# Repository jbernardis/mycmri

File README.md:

# mycmri
## DIY CMRI ecosystem for model railroad automation

This is very much a work in progress.  At this point, the following eagle designs are mature:

- blockocchexdelay - a single board with 6 DCC block occupancy detectors that immediately detect block entry, but do not report block exit until approximately 1 second after train actually leaves block.

- 2 byte input - a circuit design based on 74hc165 shift registers to pull in data from inputs such as buttons, block occupancy detectors, etc.

- 1 byte input - a 1 shift register version of the above.

- 2 byte output with darlington open collector with a darlington array in the output stream to support other devices such as motors and relays - circuit sink.

All other designs are very early in their life and have not been tested/debugged:

- node - an arduino based circuit that can shift in data from many inputs, shift out data to many outputs, drive servos through an adafruit PWM servo driver board, and report all of this back to a host PC (running JMRI?) via an RS485 bus.    This circuit may also provide 5 volt power to this ecosystem.

- 1 byte output version of the above

- relay boards designed to work with the output boards, 2 and 4 relay variants

- others as needs/inspirations arise.  Support for DCC Reverser and CD discharge unit is also being considered.

Arduino code will be provided as node functionality is implemented

Linux-based driver code is also part of this repository and is in very early development.

Slowly moving PCB design to kicad.  Both kicad and eagle designs will be included here, at least until the first boards are fabricated and tested from the kicad designs.

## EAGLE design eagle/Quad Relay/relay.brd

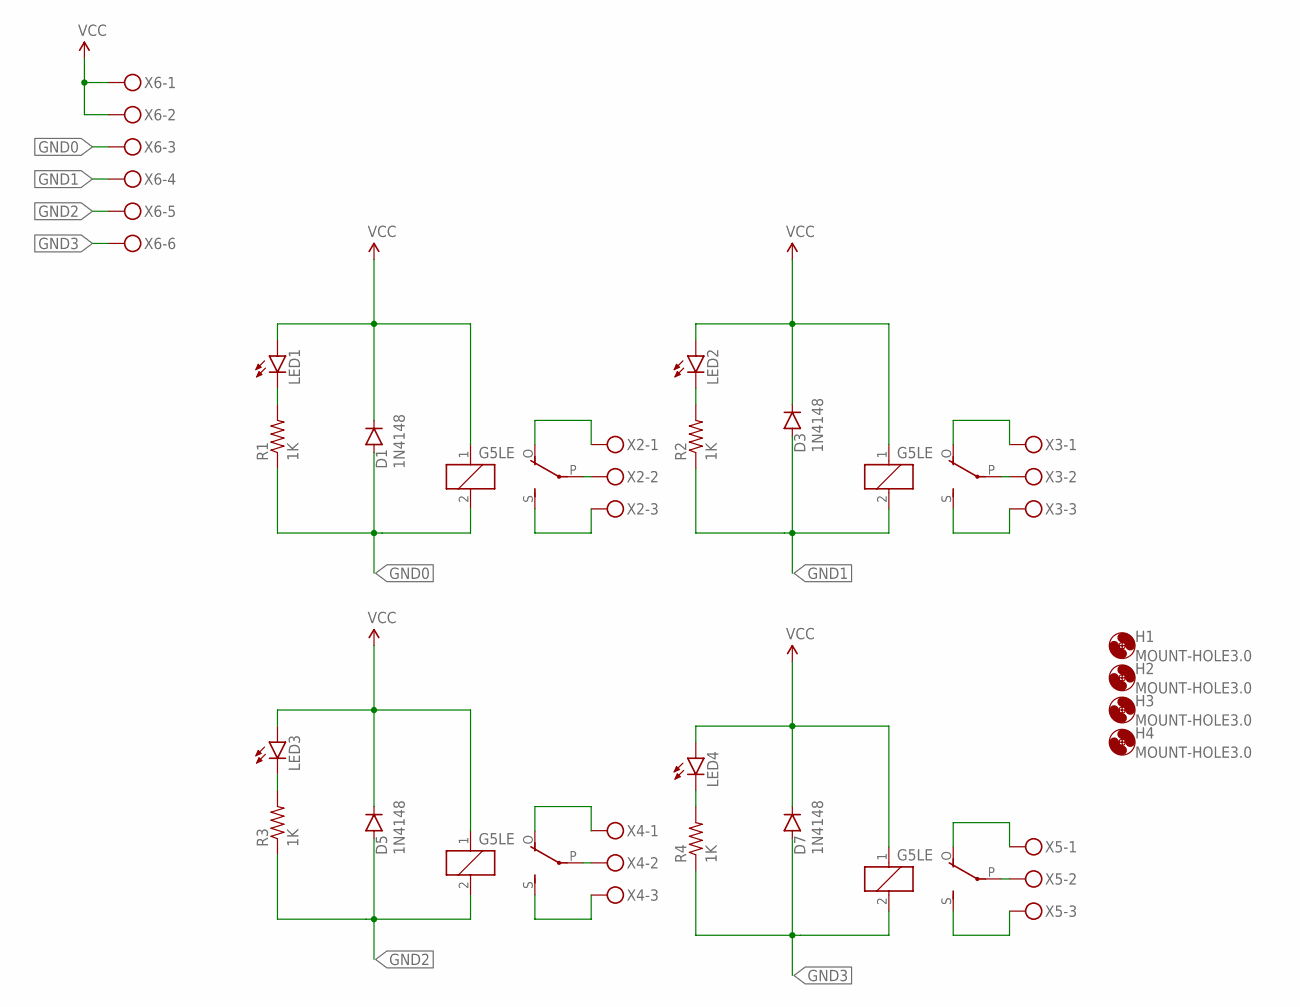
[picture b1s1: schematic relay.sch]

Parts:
D1, D3, D5, D7: 1N4148; DIODE-1N4148-KIT
H1, H2, H3, H4: MOUNT-HOLE3.0; 3,0
K1, K2, K3, K4: G5LE
LED1, LED2, LED3, LED4: LED3MM
R1, R2, R3, R4: 1K; AXIAL-0.3EZ
X2, X3, X4, X5: MKDSN1,5/3-5,08
X6: MKDSN1,5/6-5,08

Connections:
GND0: D1.A, K2.2, R1.P$1 (1), X6.3
GND1: D3.A, K1.2, R2.P$1 (1), X6.4
GND2: D5.A, K3.2, R3.P$1 (1), X6.5
GND3: D7.A, K4.2, R4.P$1 (1), X6.6
unnamed: K2.P, X2.2
unnamed: K2.S, X2.3
unnamed: K2.O, X2.1
unnamed: LED2.K (C), R2.P$2 (2)
unnamed: K1.P, X3.2
unnamed: K1.S, X3.3
unnamed: K1.O, X3.1
unnamed: LED3.K (C), R3.P$2 (2)
unnamed: LED1.K (C), R1.P$2 (2)
unnamed: K3.P, X4.2
unnamed: K3.S, X4.3
unnamed: K3.O, X4.1
unnamed: LED4.K (C), R4.P$2 (2)
unnamed: K4.P, X5.2
unnamed: K4.S, X5.3
unnamed: K4.O, X5.1
VCC: D1.C, D3.C, D5.C, D7.C, K1.1, K2.1, K3.1, K4.1, LED1.A, LED2.A, LED3.A, LED4.A, X6.1, X6.2

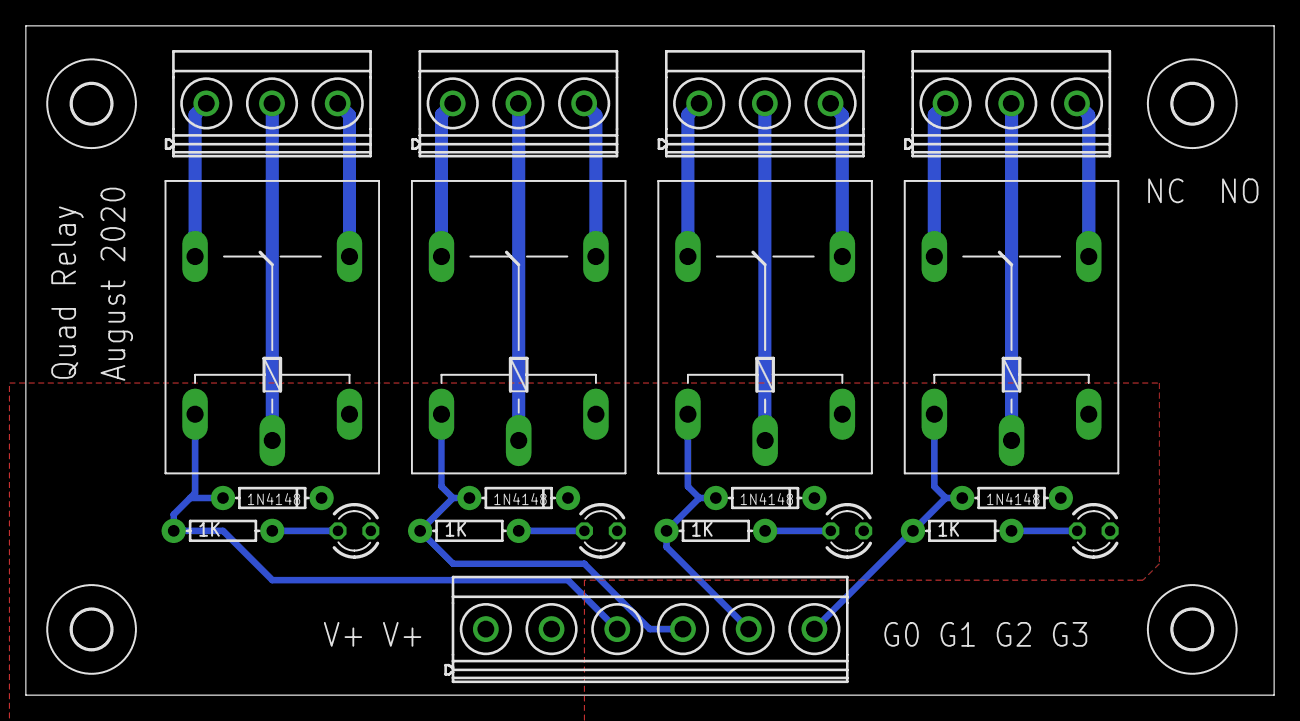
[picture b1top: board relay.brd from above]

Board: 2 copper layers, 96.5 x 51.7 mm, 25 parts (0 on the bottom side), 21 nets.

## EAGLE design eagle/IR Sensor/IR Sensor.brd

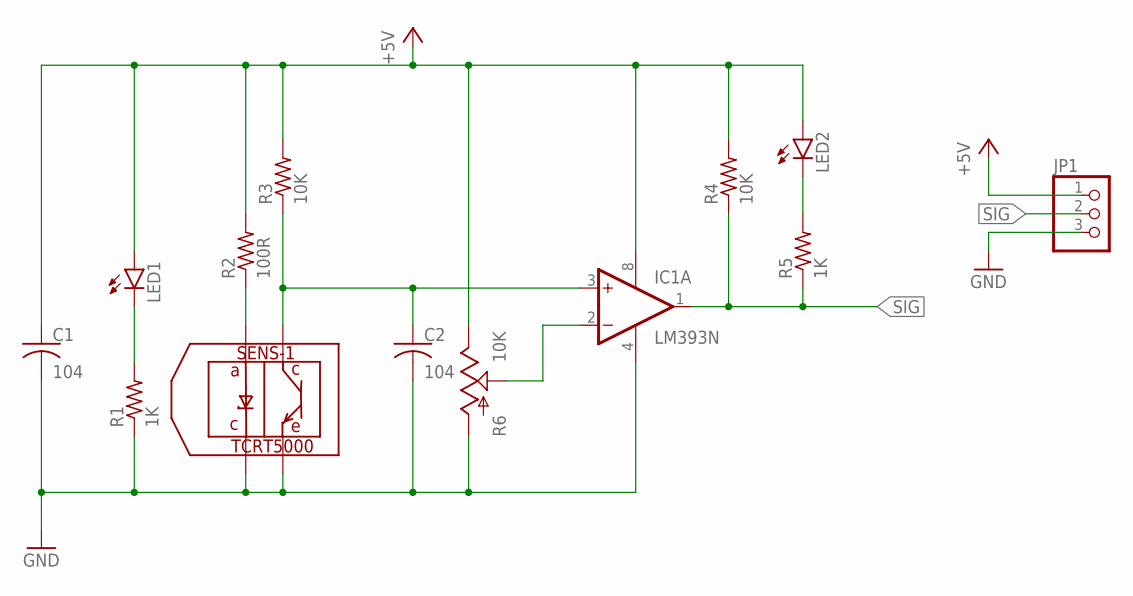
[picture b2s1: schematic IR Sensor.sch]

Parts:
C1, C2: 104; C050-045X075
IC1: LM393N; DIL08
JP1: PINHD-1X3; 1X03
LED1, LED2: LED3MM
R1, R5: 1K; 0207/7
R2: 100R; 0207/7
R3, R4: 10K; 0207/7
R6: 10K; CA6V
SENS-1: TCRT5000; 5000

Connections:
+5V: C1.1, IC1.8 (V+), JP1.1, LED1.A, LED2.A, R2.2, R3.2, R4.2, R6.E
GND: C1.2, C2.2, IC1.4 (V-), JP1.3, R1.1, R6.A, SENS-1.P$2, SENS-1.P$4
unnamed: LED1.K (C), R1.2
unnamed: IC1.2 (-IN), R6.S
unnamed: R2.1, SENS-1.P$3
unnamed: C2.1, IC1.3 (+IN), R3.1, SENS-1.P$1
unnamed: LED2.K (C), R5.2
SIG: IC1.1 (OUT), JP1.2, R4.1, R5.1

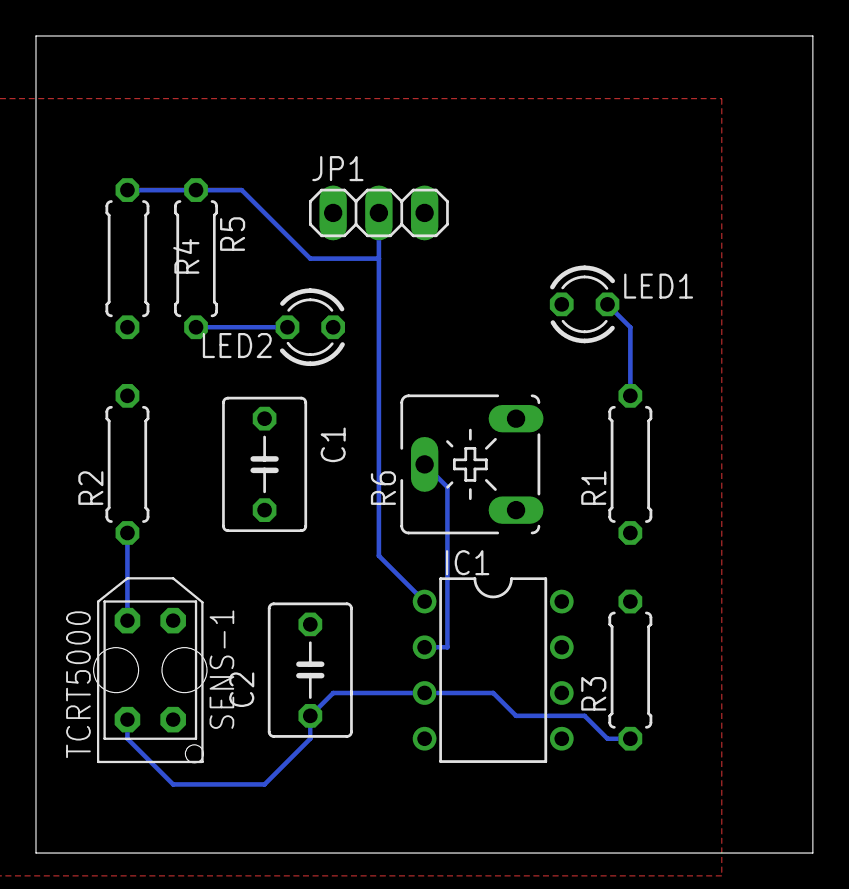
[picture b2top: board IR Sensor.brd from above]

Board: 2 copper layers, 43.2 x 45.4 mm, 13 parts (0 on the bottom side), 8 nets.

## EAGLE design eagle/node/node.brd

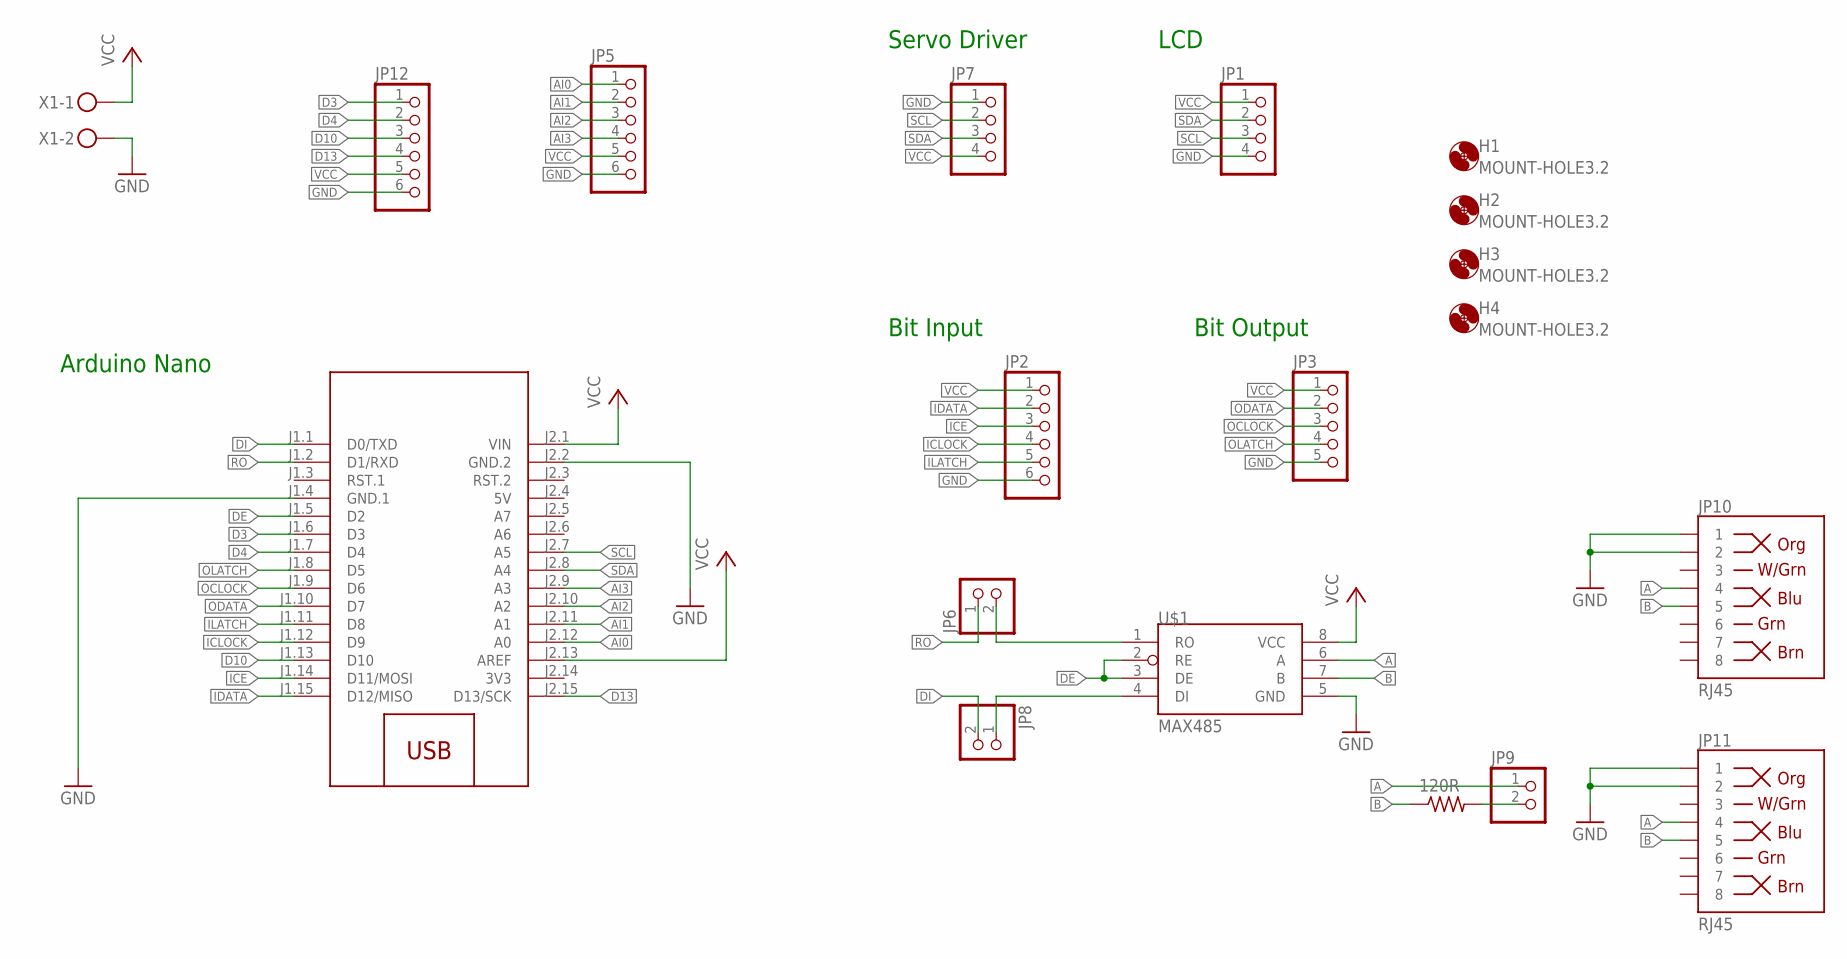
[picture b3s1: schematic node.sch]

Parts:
H1, H2, H3, H4: MOUNT-HOLE3.2; 3,2
JP1, JP7: PINHD-1X4/90; 1X04/90
JP2: PINHD-1X6/90; 1X06/90
JP3: PINHD-1X5/90; 1X05/90
JP5, JP12: PINHD-1X6; 1X06
JP6, JP8, JP9: PINHD-1X2; 1X02
JP10, JP11: RJ45; RJ45-8
M1: ARDUINO-NANO-3.0
R2: 120R; 0207/2V
U$1: MAX485; DIL08
X1: MKDSN1,5/2-5,08

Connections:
3V3: M1.J2.14 (3V3)
5V: M1.J2.4 (5V)
A: JP9.1, JP10.4, JP11.4, U$1.6 (A)
AI0: JP5.1, M1.J2.12 (A0)
AI1: JP5.2, M1.J2.11 (A1)
AI2: JP5.3, M1.J2.10 (A2)
AI3: JP5.4, M1.J2.9 (A3)
B: JP10.5, JP11.5, R2.1, U$1.7 (B)
D3: JP12.1, M1.J1.6 (D3)
D4: JP12.2, M1.J1.7 (D4)
D10: JP12.3, M1.J1.13 (D10)
D13: JP12.4, M1.J2.15 (D13/SCK)
DE: M1.J1.5 (D2), U$1.2 (RE), U$1.3 (DE)
DI: JP8.2, M1.J1.1 (D0/TXD)
GND: JP1.4, JP2.6, JP3.5, JP5.6, JP7.1, JP10.1, JP10.2, JP11.1, JP11.2, JP12.6, M1.J1.4 (GND.1), M1.J2.2 (GND.2), U$1.5 (GND), X1.2
ICE: JP2.3, M1.J1.14 (D11/MOSI)
ICLOCK: JP2.4, M1.J1.12 (D9)
IDATA: JP2.2, M1.J1.15 (D12/MISO)
ILATCH: JP2.5, M1.J1.11 (D8)
unnamed: JP9.2, R2.2
unnamed: JP6.2, U$1.1 (RO)
unnamed: JP8.1, U$1.4 (DI)
OCLOCK: JP3.3, M1.J1.9 (D6)
ODATA: JP3.2, M1.J1.10 (D7)
OLATCH: JP3.4, M1.J1.8 (D5)
RO: JP6.1, M1.J1.2 (D1/RXD)
SCL: JP1.3, JP7.2, M1.J2.7 (A5)
SDA: JP1.2, JP7.3, M1.J2.8 (A4)
VCC: JP1.1, JP2.1, JP3.1, JP5.5, JP7.4, JP12.5, M1.J2.1 (VIN), M1.J2.13 (AREF), U$1.8 (VCC), X1.1

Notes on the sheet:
Arduino Nano
Bit Input
Bit Output
Servo Driver
LCD

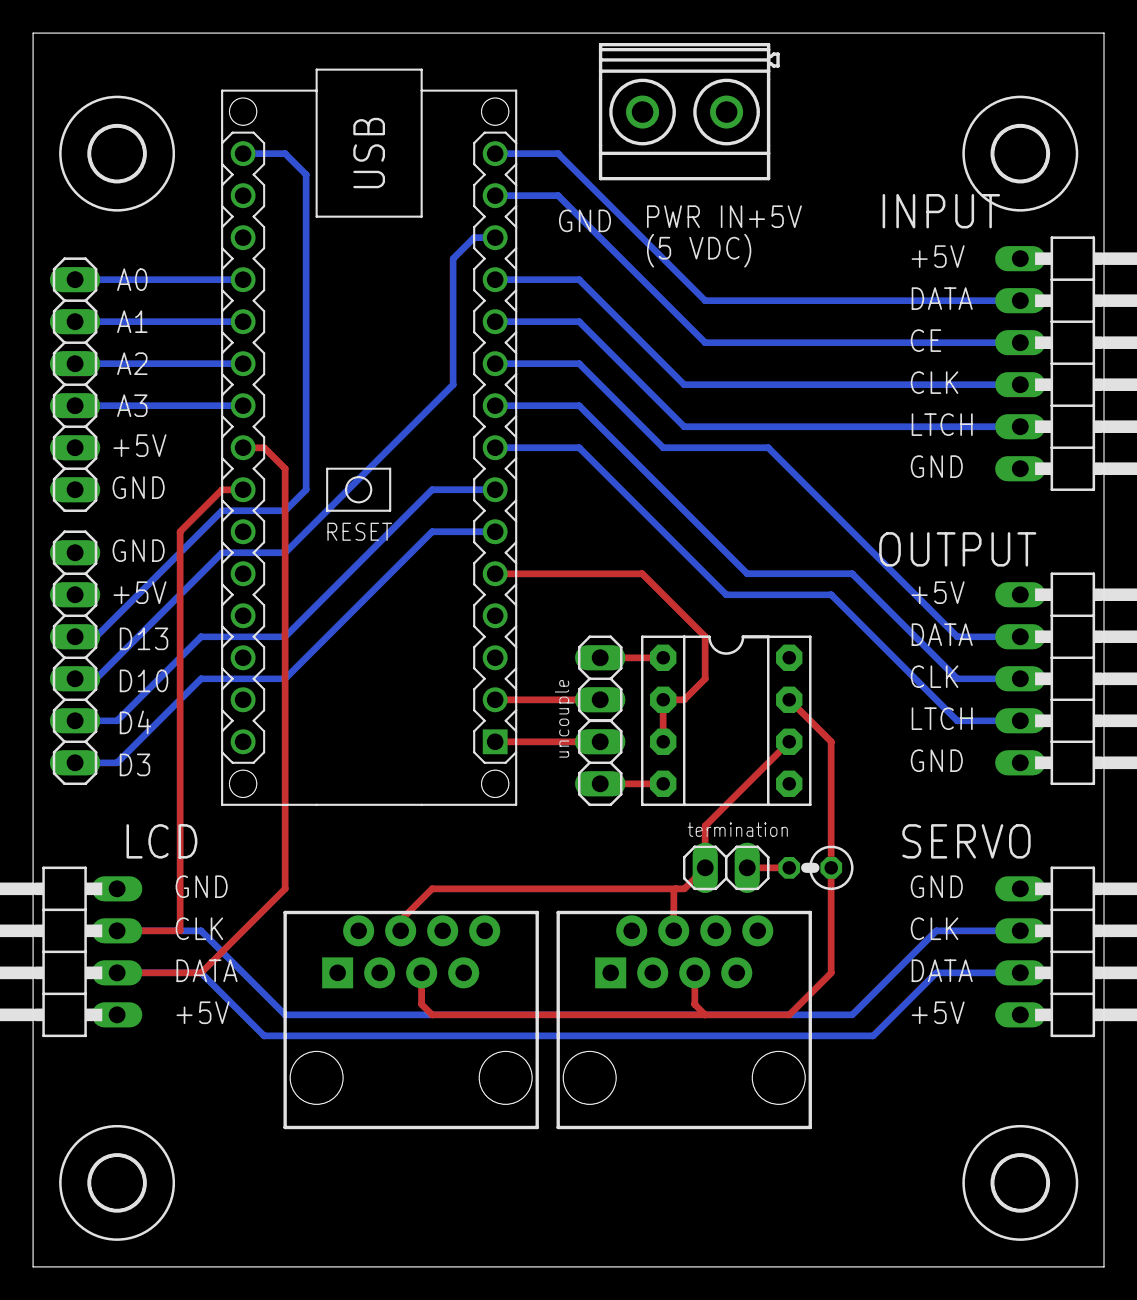
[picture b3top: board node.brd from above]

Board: 2 copper layers, 64.8 x 74.6 mm, 19 parts (0 on the bottom side), 27 nets.

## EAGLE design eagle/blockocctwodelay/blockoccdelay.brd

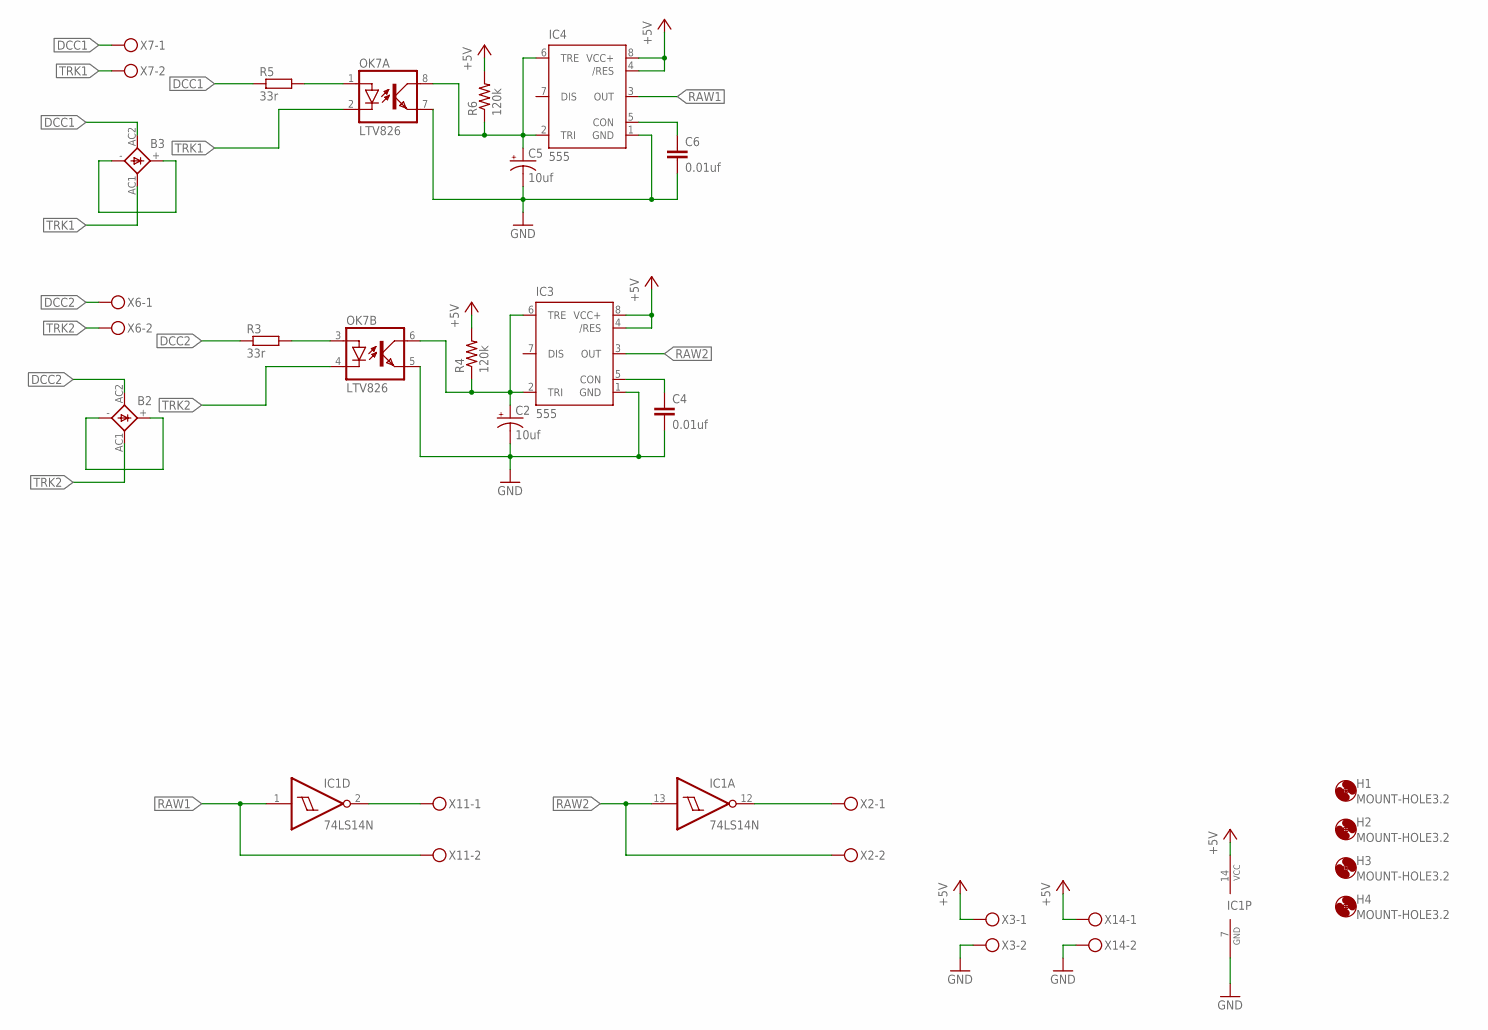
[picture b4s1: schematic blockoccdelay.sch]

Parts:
B2, B3: GBU4; GBU4S
C2, C5: 10uf; E2,5-6
C4, C6: 0.01uf; C050-035X075
H1, H2, H3, H4: MOUNT-HOLE3.2; 3,2
IC1: 74LS14N; DIL14
IC3, IC4: 555; DIP08
OK7: LTV826; DIL08
R3, R5: 33r; 0207/2V
R4, R6: 120k; 0309V
X2, X3, X6, X7, X11, X14: MKDSN1,5/2-5,08

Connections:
+5V: IC1.14 (VCC), IC3.4 (/RES), IC3.8 (VCC+), IC4.4 (/RES), IC4.8 (VCC+), R4.2, R6.2, X3.1, X14.1
DCC1: B3.AC2 (AC1), R5.1, X7.1
DCC2: B2.AC2 (AC1), R3.1, X6.1
GND: C2.-, C4.2, C5.-, C6.2, IC1.7 (GND), IC3.1 (GND), IC4.1 (GND), OK7.5 (EMIT), OK7.7 (EMIT), X3.2, X14.2
unnamed: IC1.12 (O), X2.1
unnamed: B2.+, B2.-
unnamed: OK7.3 (A), R3.2
unnamed: C4.1, IC3.5 (CON)
unnamed: B3.+, B3.-
unnamed: OK7.1 (A), R5.2
unnamed: C6.1, IC4.5 (CON)
unnamed: IC1.2 (O), X11.1
RAW1: IC1.1 (I), IC4.3 (OUT), X11.2
RAW2: IC1.13 (I), IC3.3 (OUT), X2.2
TRI1: C2.+, IC3.2 (TRI), IC3.6 (TRE), OK7.6 (COL), R4.1
TRI2: C5.+, IC4.2 (TRI), IC4.6 (TRE), OK7.8 (COL), R6.1
TRK1: B3.AC1 (AC2), OK7.2 (C), X7.2
TRK2: B2.AC1 (AC2), OK7.4 (C), X6.2

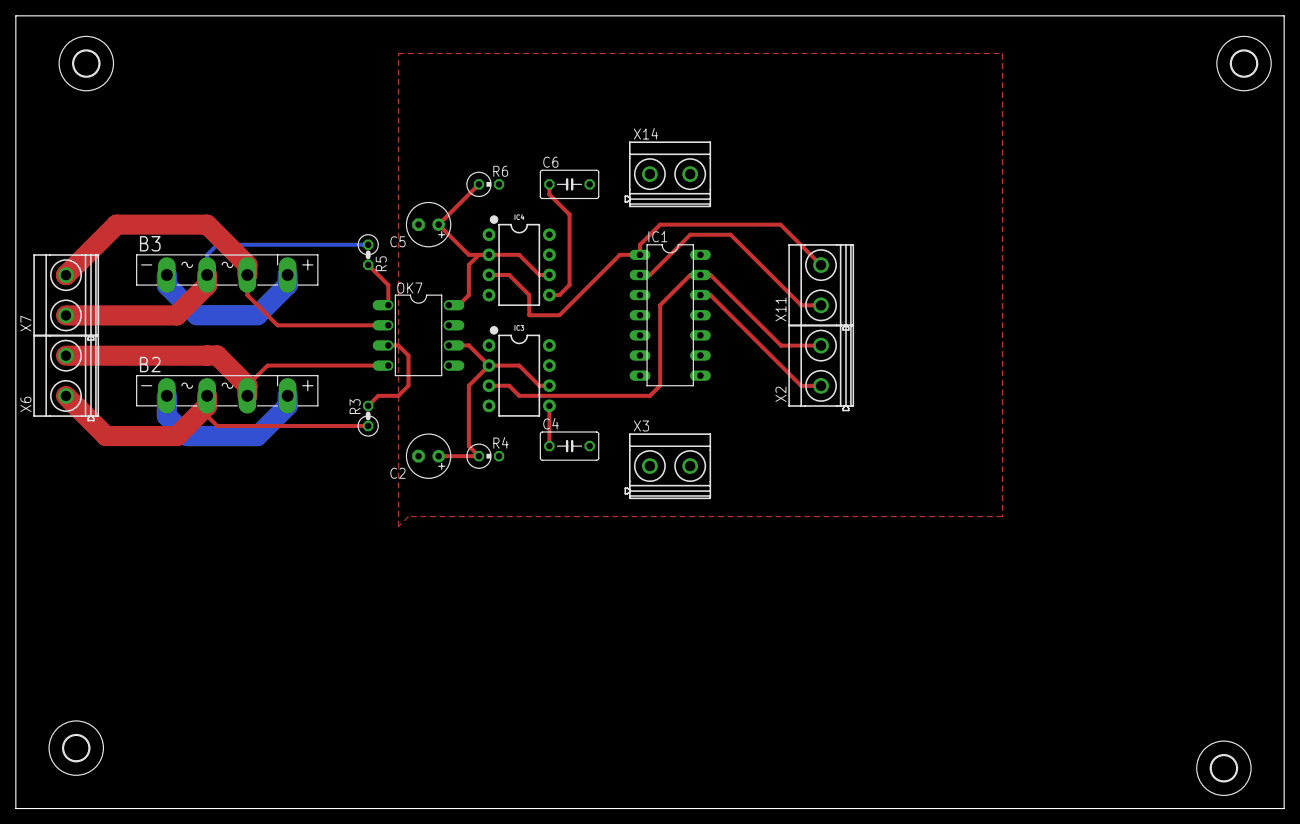
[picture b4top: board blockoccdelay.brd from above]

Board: 2 copper layers, 160.0 x 100.0 mm, 24 parts (0 on the bottom side), 18 nets.

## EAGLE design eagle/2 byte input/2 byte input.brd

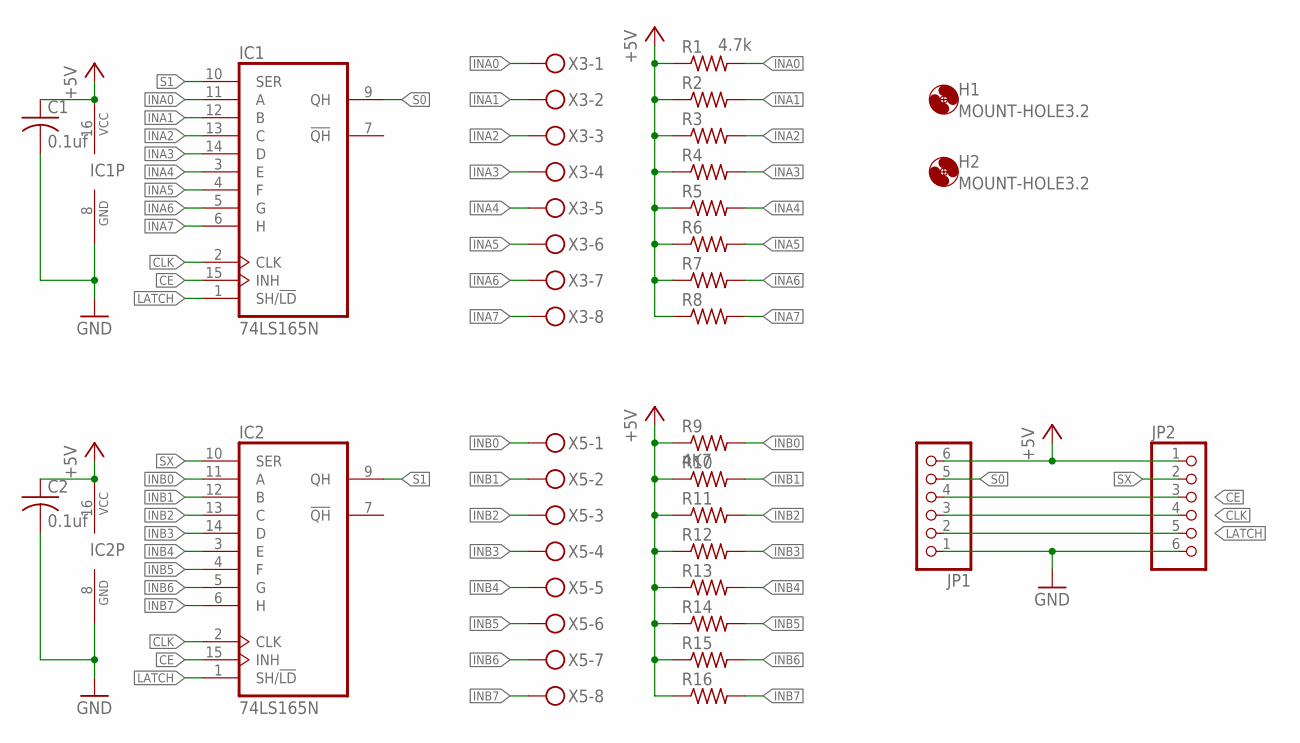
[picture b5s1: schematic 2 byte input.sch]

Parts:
C1, C2: 0.1uf; C025-025X050
H1, H2: MOUNT-HOLE3.2; 3,2
IC1, IC2: 74LS165N; DIL16
JP1, JP2: PINHD-1X6/90; 1X06/90
R1: 4.7k; 0207/2V
R2, R3, R4, R5, R6, R7, R8, R10, R11, R12, R13, R14, R15, R16: R-US_0207/2V; 0207/2V
R9: 4K7; 0207/2V
X3, X5: MKDSN1,5/8-5,08

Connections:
+5V: C1.1, C2.1, IC1.16 (VCC), IC2.16 (VCC), JP1.6, JP2.1, R1.1, R2.1, R3.1, R4.1, R5.1, R6.1, R7.1, R8.1, R9.1, R10.1, R11.1, R12.1, R13.1, R14.1, R15.1, R16.1
CE: IC1.15 (INH), IC2.15 (INH), JP1.4, JP2.3
CLK: IC1.2 (CLK), IC2.2 (CLK), JP1.3, JP2.4
GND: C1.2, C2.2, IC1.8 (GND), IC2.8 (GND), JP1.1, JP2.6
INA0: IC1.11 (A), R1.2, X3.1
INA1: IC1.12 (B), R2.2, X3.2
INA2: IC1.13 (C), R3.2, X3.3
INA3: IC1.14 (D), R4.2, X3.4
INA4: IC1.3 (E), R5.2, X3.5
INA5: IC1.4 (F), R6.2, X3.6
INA6: IC1.5 (G), R7.2, X3.7
INA7: IC1.6 (H), R8.2, X3.8
INB0: IC2.11 (A), R9.2, X5.1
INB1: IC2.12 (B), R10.2, X5.2
INB2: IC2.13 (C), R11.2, X5.3
INB3: IC2.14 (D), R12.2, X5.4
INB4: IC2.3 (E), R13.2, X5.5
INB5: IC2.4 (F), R14.2, X5.6
INB6: IC2.5 (G), R15.2, X5.7
INB7: IC2.6 (H), R16.2, X5.8
LATCH: IC1.1 (SH/!LD), IC2.1 (SH/!LD), JP1.2, JP2.5
S0: IC1.9 (QH), JP1.5
S1: IC1.10 (SER), IC2.9 (QH)
SX: IC2.10 (SER), JP2.2

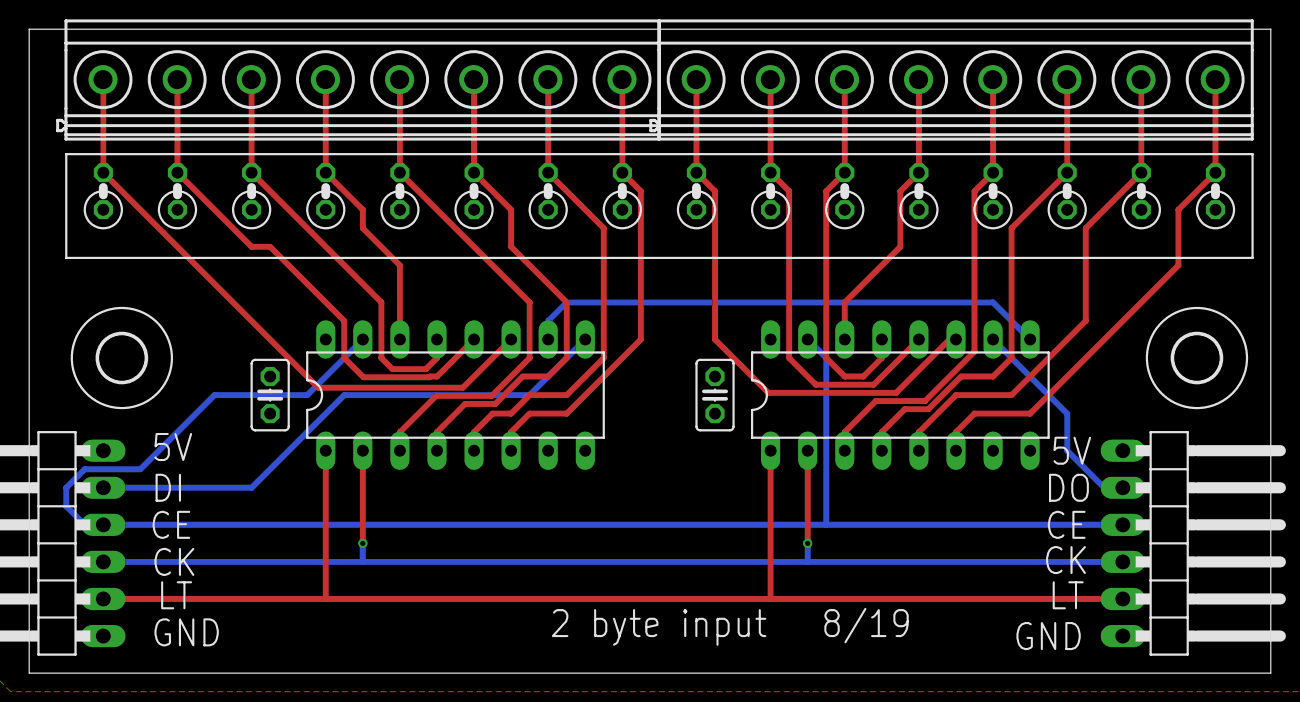
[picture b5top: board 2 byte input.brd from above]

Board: 2 copper layers, 85.1 x 44.1 mm, 26 parts (0 on the bottom side), 24 nets.

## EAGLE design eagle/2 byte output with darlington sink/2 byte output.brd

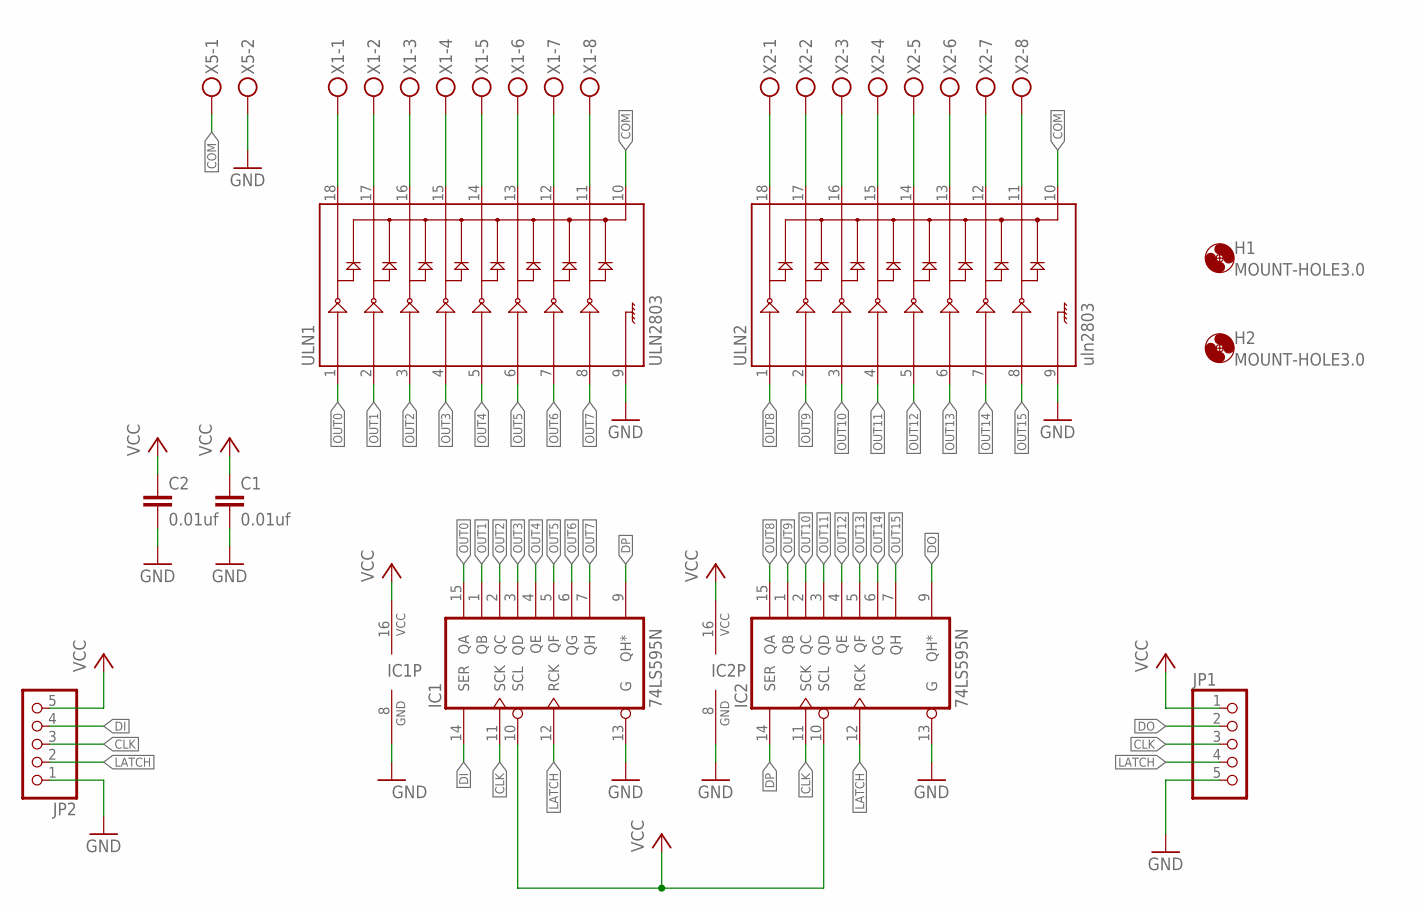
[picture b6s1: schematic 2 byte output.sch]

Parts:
C1, C2: 0.01uf; C050-035X075
H1, H2: MOUNT-HOLE3.0; 3,0
IC1, IC2: 74LS595N; DIL16
JP1, JP2: PINHD-1X5/90; 1X05/90
ULN1: ULN2803; DIL18
ULN2: uln2803; DIL18
X1, X2: MKDSN1,5/8-5,08
X5: MKDSN1,5/2-5,08

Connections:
CLK: IC1.11 (SCK), IC2.11 (SCK), JP1.3, JP2.3
COM: ULN1.10, ULN2.10, X5.1
DI: IC1.14 (SER), JP2.4
DO: IC2.9 (QH*), JP1.2
DP: IC1.9 (QH*), IC2.14 (SER)
GND: C1.2, C2.2, IC1.8 (GND), IC1.13 (G), IC2.8 (GND), IC2.13 (G), JP1.5, JP2.1, ULN1.9, ULN2.9, X5.2
LATCH: IC1.12 (RCK), IC2.12 (RCK), JP1.4, JP2.2
unnamed: ULN1.18, X1.1
unnamed: ULN1.17, X1.2
unnamed: ULN1.16, X1.3
unnamed: ULN1.15, X1.4
unnamed: ULN1.14, X1.5
unnamed: ULN1.13, X1.6
unnamed: ULN1.12, X1.7
unnamed: ULN1.11, X1.8
unnamed: ULN2.18, X2.1
unnamed: ULN2.17, X2.2
unnamed: ULN2.16, X2.3
unnamed: ULN2.15, X2.4
unnamed: ULN2.14, X2.5
unnamed: ULN2.13, X2.6
unnamed: ULN2.12, X2.7
unnamed: ULN2.11, X2.8
OUT0: IC1.15 (QA), ULN1.1
OUT1: IC1.1 (QB), ULN1.2
OUT2: IC1.2 (QC), ULN1.3
OUT3: IC1.3 (QD), ULN1.4
OUT4: IC1.4 (QE), ULN1.5
OUT5: IC1.5 (QF), ULN1.6
OUT6: IC1.6 (QG), ULN1.7
OUT7: IC1.7 (QH), ULN1.8
OUT8: IC2.15 (QA), ULN2.1
OUT9: IC2.1 (QB), ULN2.2
OUT10: IC2.2 (QC), ULN2.3
OUT11: IC2.3 (QD), ULN2.4
OUT12: IC2.4 (QE), ULN2.5
OUT13: IC2.5 (QF), ULN2.6
OUT14: IC2.6 (QG), ULN2.7
OUT15: IC2.7 (QH), ULN2.8
VCC: C1.1, C2.1, IC1.10 (SCL), IC1.16 (VCC), IC2.10 (SCL), IC2.16 (VCC), JP1.1, JP2.5

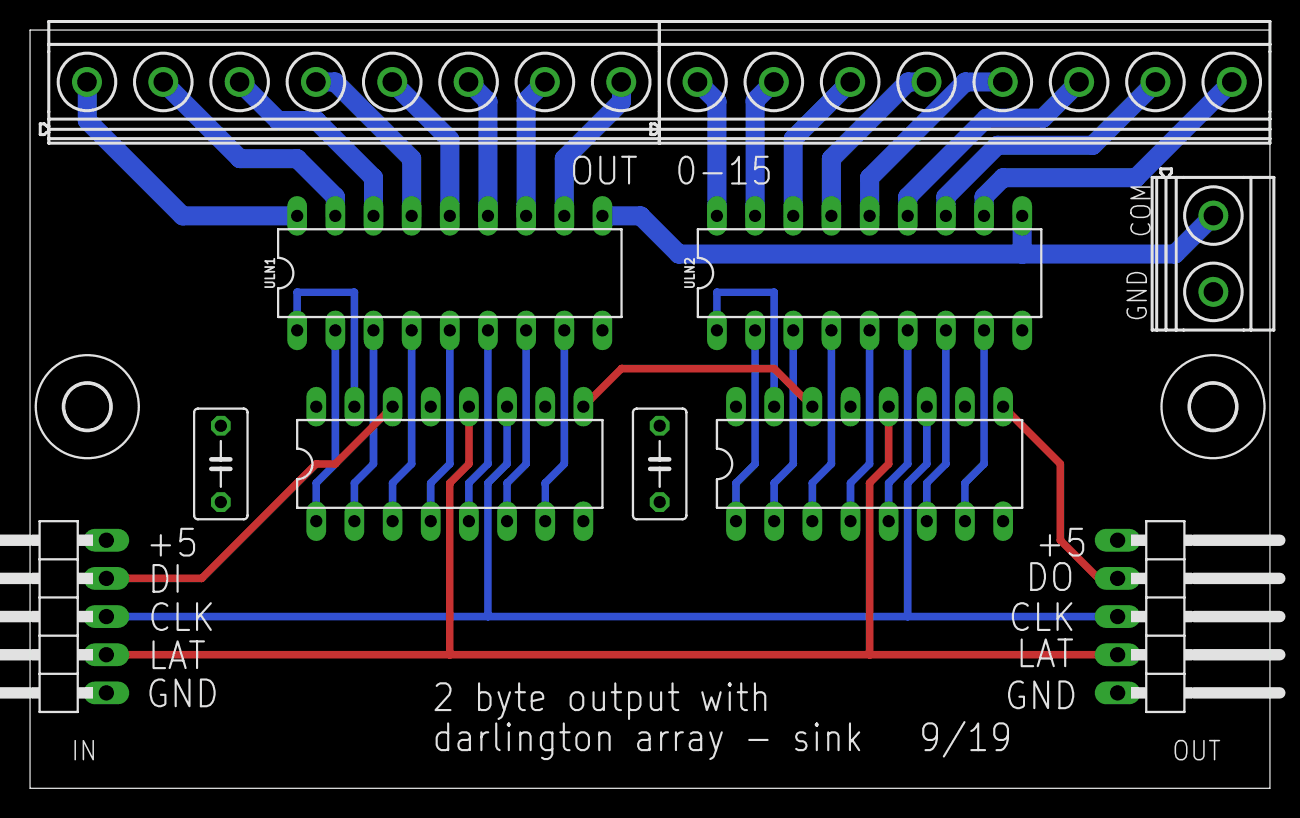
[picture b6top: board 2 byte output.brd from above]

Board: 2 copper layers, 82.5 x 50.5 mm, 13 parts (0 on the bottom side), 40 nets.

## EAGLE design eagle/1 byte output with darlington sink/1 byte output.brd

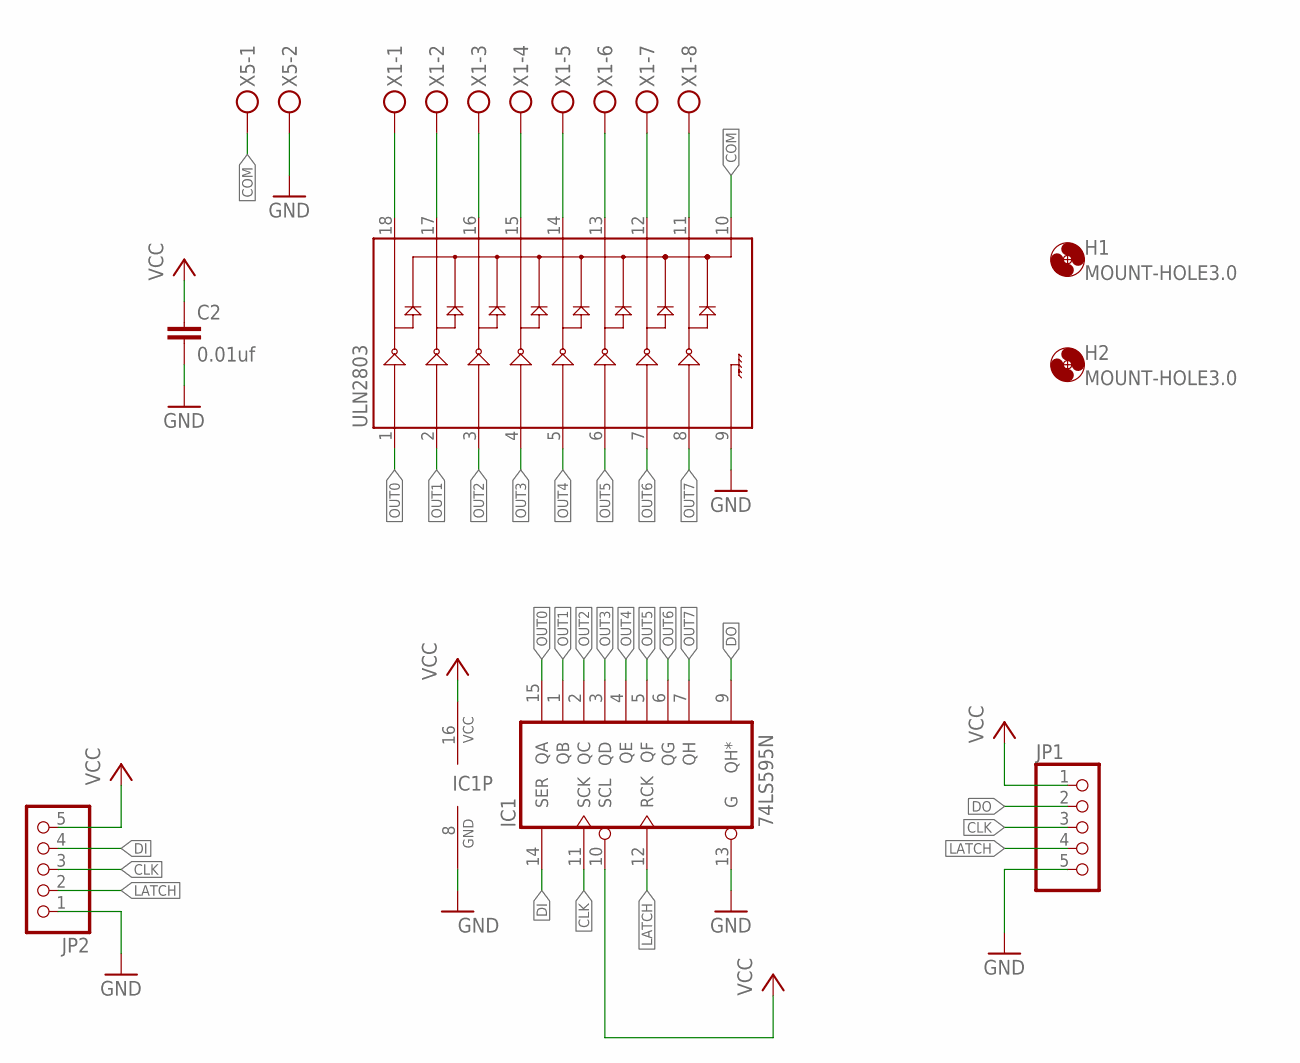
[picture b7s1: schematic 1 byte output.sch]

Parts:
C2: 0.01uf; C050-035X075
H1, H2: MOUNT-HOLE3.0; 3,0
IC1: 74LS595N; DIL16
JP1, JP2: PINHD-1X5/90; 1X05/90
ULN2803: ULN2803DIP; DIL18
X1: MKDSN1,5/8-5,08
X5: MKDSN1,5/2-5,08

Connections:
CLK: IC1.11 (SCK), JP1.3, JP2.3
COM: ULN2803.10, X5.1
DI: IC1.14 (SER), JP2.4
DO: IC1.9 (QH*), JP1.2
GND: C2.2, IC1.8 (GND), IC1.13 (G), JP1.5, JP2.1, ULN2803.9, X5.2
LATCH: IC1.12 (RCK), JP1.4, JP2.2
unnamed: ULN2803.18, X1.1
unnamed: ULN2803.17, X1.2
unnamed: ULN2803.16, X1.3
unnamed: ULN2803.15, X1.4
unnamed: ULN2803.14, X1.5
unnamed: ULN2803.13, X1.6
unnamed: ULN2803.12, X1.7
unnamed: ULN2803.11, X1.8
OUT0: IC1.15 (QA), ULN2803.1
OUT1: IC1.1 (QB), ULN2803.2
OUT2: IC1.2 (QC), ULN2803.3
OUT3: IC1.3 (QD), ULN2803.4
OUT4: IC1.4 (QE), ULN2803.5
OUT5: IC1.5 (QF), ULN2803.6
OUT6: IC1.6 (QG), ULN2803.7
OUT7: IC1.7 (QH), ULN2803.8
VCC: C2.1, IC1.10 (SCL), IC1.16 (VCC), JP1.1, JP2.5

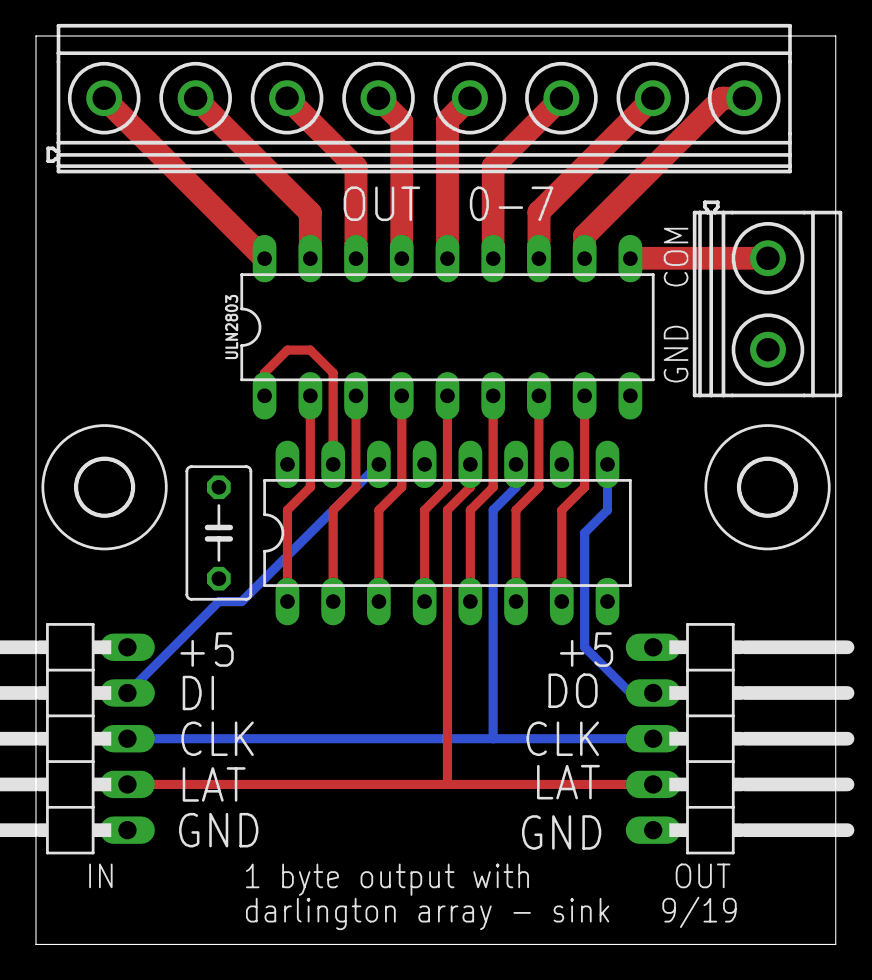
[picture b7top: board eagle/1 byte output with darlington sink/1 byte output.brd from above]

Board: 2 copper layers, 44.4 x 50.5 mm, 9 parts (0 on the bottom side), 23 nets.

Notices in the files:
parts and their libraries:
SparkFun-IC-Special-Function: Licensing: Creative Commons ShareAlike 4.0 International - https://creativecommons.org/licenses/by-sa/4.0
SparkFun-Aesthetics: Licensing: CC v3.0 Share-Alike You are welcome to use this library for commercial purposes.
